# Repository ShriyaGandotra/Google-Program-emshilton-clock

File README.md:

# emshilton-clock
As a part of Google Hardware Sprint Program :
 - Developed Schematic of my clock.
 - Designed PCB using KiCAD software.
 - Followed by testing and documentation of the product.

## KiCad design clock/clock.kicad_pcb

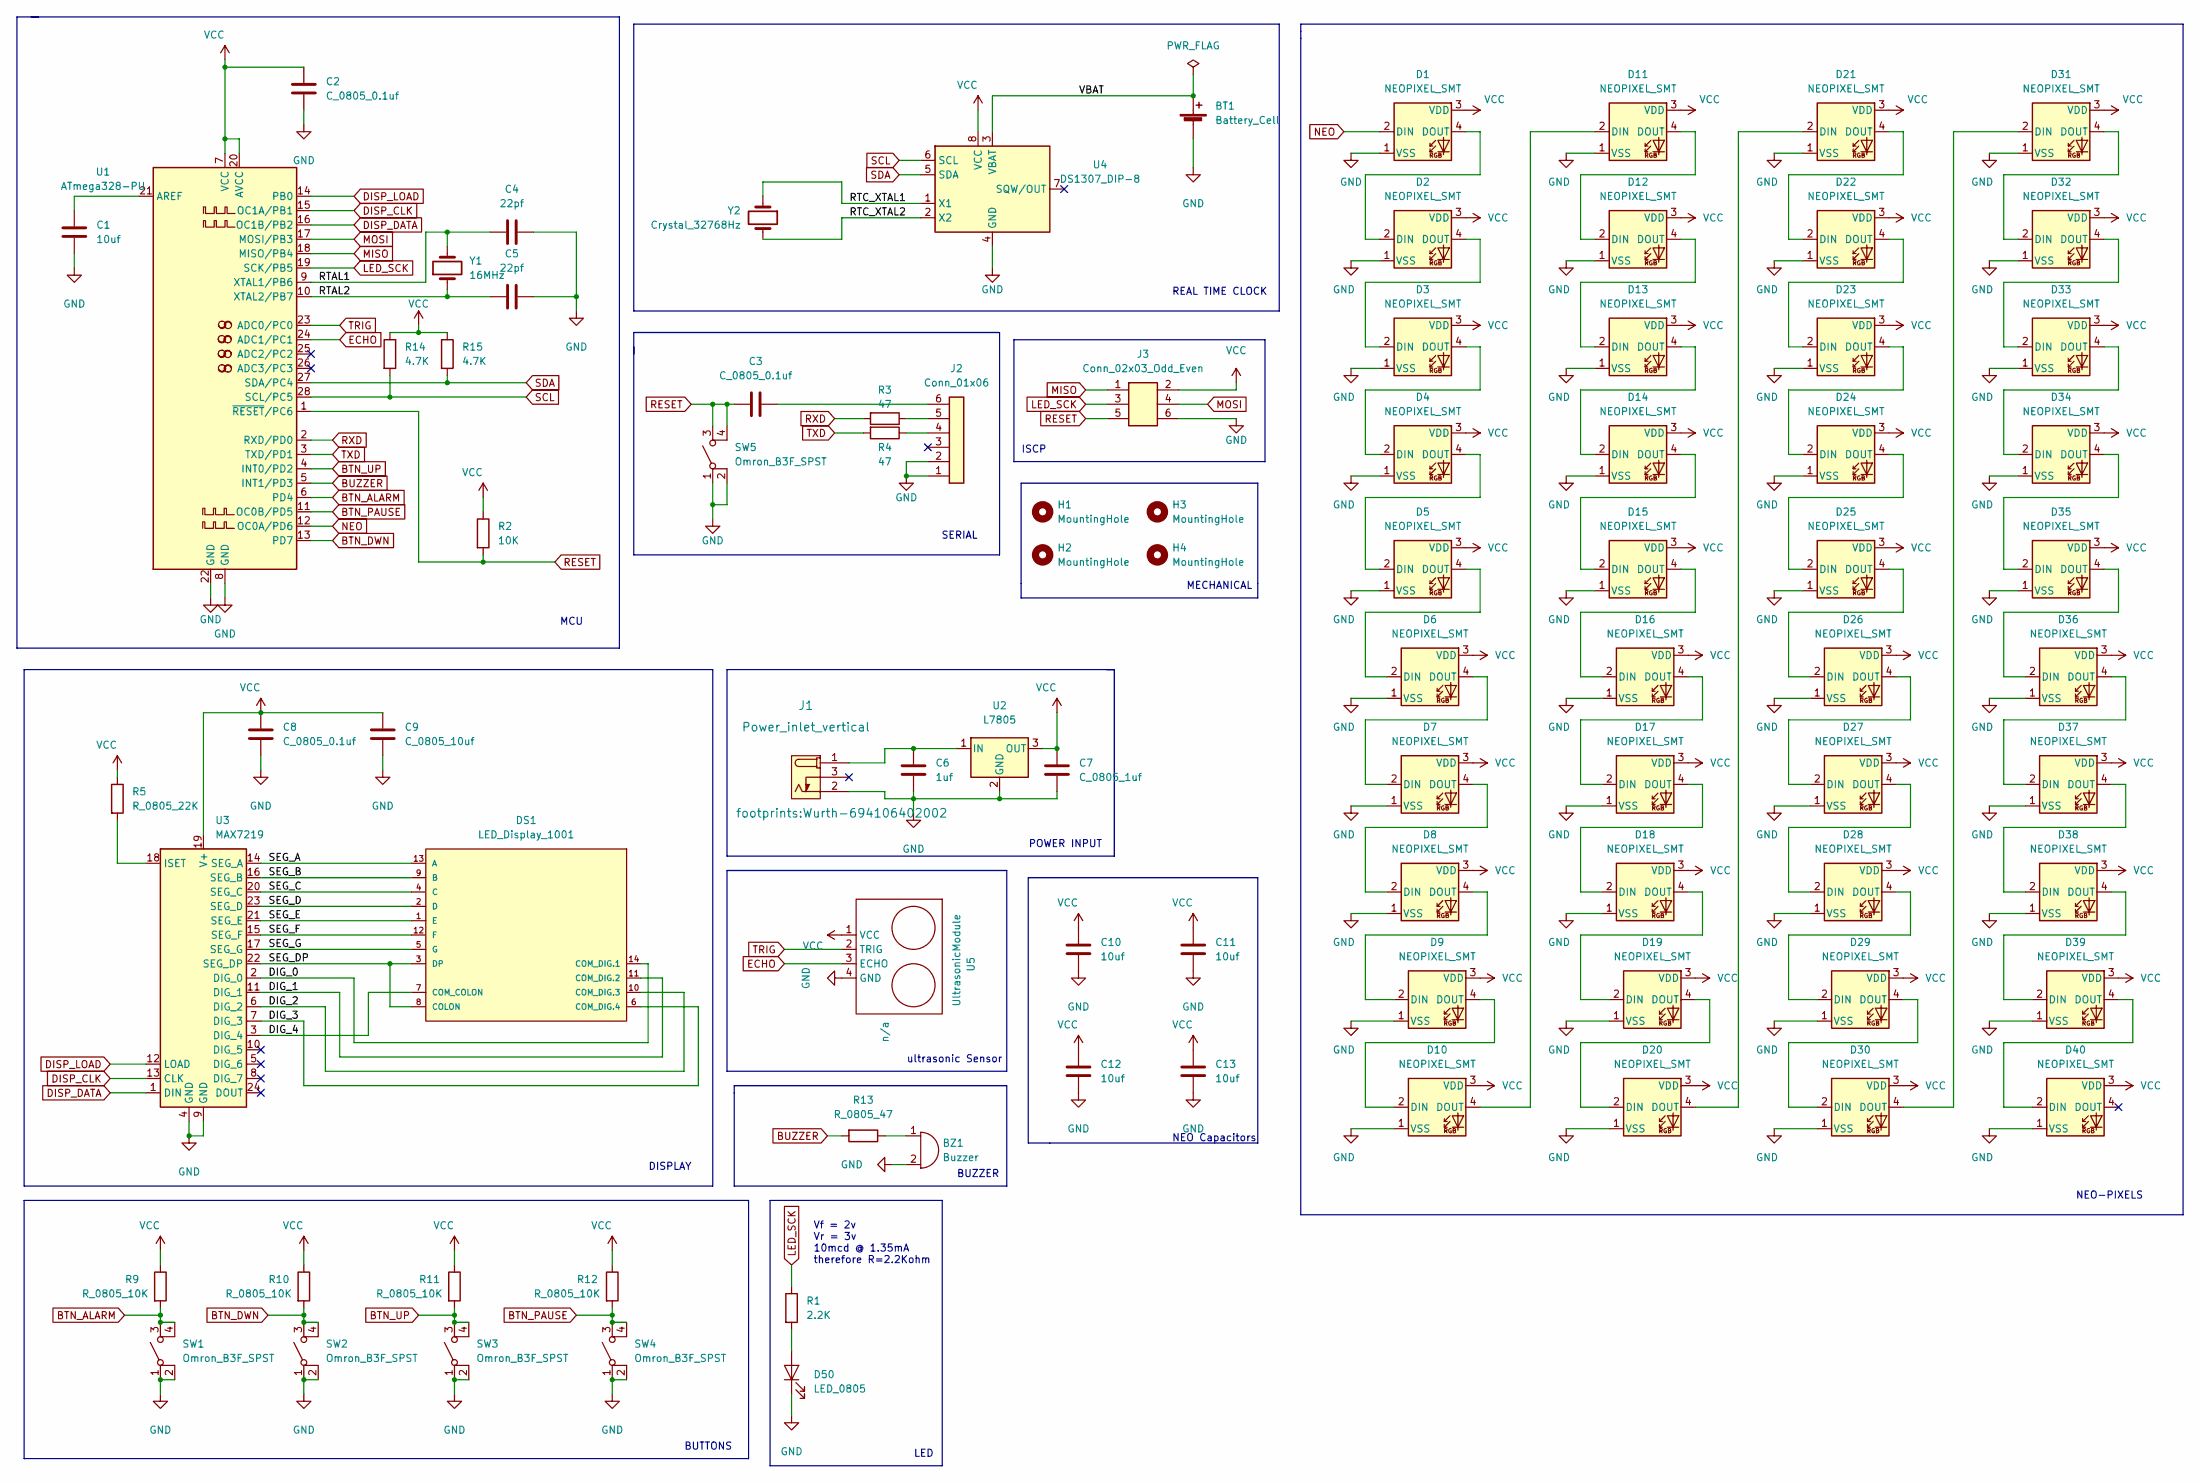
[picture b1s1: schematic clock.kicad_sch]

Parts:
BT1: Battery_Cell; BatteryHolder_Keystone_106_1x20mm; MPN BS-7; Digikey PN BS-7-ND
BZ1: Buzzer; Buzzer_TDK_PS1240P02BT_D12.2mm_H6.5mm; MPN PS1420P02CT; Digikey PN 445-2526-1-ND
C1, C10, C11, C12, C13: 10uf; C_0805_2012Metric; Voltage N/A; Tolerance N/A; MPN GRM21BR61E106KA73L; Digikey PN 490-5523-1-ND
C2, C3, C8: C_0805_0.1uf; C_0805_2012Metric; Voltage N/A; Tolerance N/A; MPN CC0805KKX7R8BB105; Digikey PN 311-1456-1-ND
C4, C5: 22pf; C_0805_2012Metric; Voltage N/A; Tolerance N/A; MPN CC0805JRNPO9BN220; Digikey PN 311-1103-1-ND
C6: 1uf; C_0805_2012Metric; Voltage N/A; Tolerance N/A; MPN CC0805KKX7R8BB105; Digikey PN 311-1456-1-ND
C7: C_0805_1uf; C_0805_2012Metric; Voltage N/A; Tolerance N/A; MPN CC0805KKX7R8BB105; Digikey PN 311-1456-1-ND
C9: C_0805_10uf; C_0805_2012Metric; Voltage N/A; Tolerance N/A; MPN GRM21BR61E106KA73L; Digikey PN 490-5523-1-ND
D1, D2, D3, D4, D5, D6, D7, D8, D9, D10, D11, D12, D13, D14, D15, D16, D17, D18, D19, D20, D21, D22, D23, D24, D25, D26, D27, D28, D29, D30, D31, D32, D33, D34, D35, D36, D37, D38, D39, D40: NEOPIXEL_SMT; LED_SK6812_PLCC4_5.0x5.0mm_P3.2mm; MPN IN-PI554FCH; Digikey PN 1830-1106-1-ND
D50: LED_0805; LED_0805_2012Metric; MPN 150080RS75000; Digikey PN 732-4984-1-ND
DS1: LED_Display_1001; Adafruit-1001-0-0-MFG; forward voltage 3.2V; reverse voltage 5V; mouser part number 485-1001; digikey description WHITE 7-SEGMENT CLOCK DISPLAY
H1, H2, H3, H4: MountingHole; MountingHole_3.2mm_M3
J1: Power_inlet_vertical; Wurth-694106402002; MPN 694106402002; Digikey PN 732-5931-ND
J2: Conn_01x06; PinHeader_1x06_P2.54mm_Vertical; MPN 61300611121; Digikey PN 732-5319-ND
J3: Conn_02x03_Odd_Even; PinHeader_2x03_P2.54mm_Vertical; MPN PRPC003DAAN-RC; Digikey PN S2011EC-03-ND
R1: 2.2K; R_0805_2012Metric; Tolerance N/A; MPN N/A; Digikey PN 311-2.20KCRCT-ND
R2: 10K; R_0805_2012Metric; Tolerance N/A; MPN RC0805FR-0710KL; Digikey PN 311-10.0KCRCT-ND
R3, R4: 47; R_0805_2012Metric; Tolerance N/A; Mouser PN N/A; Digikey PN RC0805FR-0747RL
R5: R_0805_22K; R_0805_2012Metric; Tolerance N/A; MPN RC0805FR-0722KL; Digikey PN 311-22.0KCRCT-ND
R9, R10, R11, R12: R_0805_10K; R_0805_2012Metric; Tolerance N/A; MPN RC0805FR-0710KL; Digikey PN 311-10.0KCRCT-ND
R13: R_0805_47; R_0805_2012Metric; Tolerance N/A; Mouser PN N/A; Digikey PN RC0805FR-0747RL
R14, R15: 4.7K; R_0805_2012Metric; Tolerance N/A; MPN RC0805FR-074K7L; Digikey PN 311-4.70KCRCT-ND
SW1, SW2, SW3, SW4, SW5: Omron_B3F_SPST; SW_SPST_Omron_B3FS-100xP; MPN B3FS-1000P; Digikey PN SW423CT-ND
U1: ATmega328-PU; DIP-28_W7.62mm; MPN ED281DT; Digikey PN ED3050-5-ND
U2: L7805; TO-252-2; MPN L7805CDT-TR; Digikey PN 497-7255-1-ND
U3: MAX7219; DIP-24_W7.62mm; MPN ED241DT; Digikey PN ED3049-5-ND
U4: DS1307_DIP-8; DIP-8_W7.62mm; MPN A 08-LC-TT; Digikey PN AE9986-ND
U5: UltrasonicModule; HC-SR04_Horiz; Digikey PN n/a
Y1: 16MHz; Crystal_SMD_HC49-SD; MPN ECS-160-20-5PXDN-TR; Digikey PN XC1299CT-ND
Y2: Crystal_32768Hz; Crystal_SMD_2Pin_3.2x1.5mm; MPN Q 0,032768-JTX310-12,5-20-T1-HMR-50K-LF; Digikey PN 1908-1314-1-ND

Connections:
/DIG_0: DS1.14 (COM_DIG.1), U3.2 (DIG_0)
/DIG_1: DS1.11 (COM_DIG.2), U3.11 (DIG_1)
/DIG_4: DS1.7 (COM_COLON), U3.3 (DIG_4)
/RTAL1: C4.2, U1.9 (XTAL1/PB6), Y1.2
/RTAL2: C5.2, U1.10 (XTAL2/PB7), Y1.1
/RTC_XTAL1: U4.1 (X1), Y2.1
/RTC_XTAL2: U4.2 (X2), Y2.2
/SEG_A: DS1.13 (A), U3.14 (SEG_A)
/SEG_B: DS1.9 (B), U3.16 (SEG_B)
/SEG_C: DS1.4 (C), U3.20 (SEG_C)
/SEG_D: DS1.2 (D), U3.23 (SEG_D)
/SEG_DP: DS1.3 (DP), DS1.8 (COLON), U3.22 (SEG_DP)
/SEG_E: DS1.1 (E), U3.21 (SEG_E)
/SEG_F: DS1.12 (F), U3.15 (SEG_F)
/SEG_G: DS1.5 (G), U3.17 (SEG_G)
/VBAT: BT1.1 (+), U4.3 (VBAT)
BTN_ALARM: R9.2, SW1.3 (B), SW1.4 (B), U1.6 (PD4)
BTN_DWN: R10.2, SW2.3 (B), SW2.4 (B), U1.13 (PD7)
BTN_PAUSE: R12.2, SW4.3 (B), SW4.4 (B), U1.11 (OC0B/PD5)
BTN_UP: R11.2, SW3.3 (B), SW3.4 (B), U1.4 (INT0/PD2)
BUZZER: R13.2, U1.5 (INT1/PD3)
DISP_CLK: U1.15 (OC1A/PB1), U3.13 (CLK)
DISP_DATA: U1.16 (OC1B/PB2), U3.1 (DIN)
DISP_LOAD: U1.14 (PB0), U3.12 (LOAD)
ECHO: U1.24 (ADC1/PC1), U5.3 (ECHO)
LED_SCK: J3.3, R1.1, U1.19 (SCK/PB5)
MISO: J3.1, U1.18 (MISO/PB4)
MOSI: J3.4, U1.17 (MOSI/PB3)
NEO: D1.2 (DIN), U1.12 (OC0A/PD6)
unnamed: BZ1.1 (-), R13.1
unnamed: C1.1, U1.21 (AREF)
unnamed: C3.1, J2.6
unnamed: C6.1, J1.1 (POLE), U2.1 (IN)
unnamed: D1.4 (DOUT), D2.2 (DIN)
unnamed: D2.4 (DOUT), D3.2 (DIN)
unnamed: D3.4 (DOUT), D4.2 (DIN)
unnamed: D4.4 (DOUT), D5.2 (DIN)
unnamed: D5.4 (DOUT), D6.2 (DIN)
unnamed: D6.4 (DOUT), D7.2 (DIN)
unnamed: D7.4 (DOUT), D8.2 (DIN)
unnamed: D8.4 (DOUT), D9.2 (DIN)
unnamed: D9.4 (DOUT), D10.2 (DIN)
unnamed: D10.4 (DOUT), D11.2 (DIN)
unnamed: D11.4 (DOUT), D12.2 (DIN)
unnamed: D12.4 (DOUT), D13.2 (DIN)
unnamed: D13.4 (DOUT), D14.2 (DIN)
unnamed: D14.4 (DOUT), D15.2 (DIN)
unnamed: D15.4 (DOUT), D16.2 (DIN)
unnamed: D16.4 (DOUT), D17.2 (DIN)
unnamed: D17.4 (DOUT), D18.2 (DIN)
unnamed: D18.4 (DOUT), D19.2 (DIN)
unnamed: D19.4 (DOUT), D20.2 (DIN)
unnamed: D20.4 (DOUT), D21.2 (DIN)
unnamed: D21.4 (DOUT), D22.2 (DIN)
unnamed: D22.4 (DOUT), D23.2 (DIN)
unnamed: D23.4 (DOUT), D24.2 (DIN)
unnamed: D24.4 (DOUT), D25.2 (DIN)
unnamed: D25.4 (DOUT), D26.2 (DIN)
unnamed: D26.4 (DOUT), D27.2 (DIN)
unnamed: D27.4 (DOUT), D28.2 (DIN)
unnamed: D28.4 (DOUT), D29.2 (DIN)
unnamed: D29.4 (DOUT), D30.2 (DIN)
unnamed: D30.4 (DOUT), D31.2 (DIN)
unnamed: D31.4 (DOUT), D32.2 (DIN)
unnamed: D32.4 (DOUT), D33.2 (DIN)
unnamed: D33.4 (DOUT), D34.2 (DIN)
unnamed: D34.4 (DOUT), D35.2 (DIN)
unnamed: D35.4 (DOUT), D36.2 (DIN)
unnamed: D36.4 (DOUT), D37.2 (DIN)
unnamed: D37.4 (DOUT), D38.2 (DIN)
unnamed: D38.4 (DOUT), D39.2 (DIN)
unnamed: D39.4 (DOUT), D40.2 (DIN)
unnamed: D50.2 (A), R1.2
unnamed: J2.4, R4.1
unnamed: J2.5, R3.1
unnamed: R5.2, U3.18 (ISET)
RESET: C3.2, J3.5, R2.2, SW5.3 (B), SW5.4 (B), U1.1 (~RESET/PC6)
RXD: R3.2, U1.2 (RXD/PD0)
SCL: R14.2, U1.28 (SCL/PC5), U4.6 (SCL)
SDA: R15.2, U1.27 (SDA/PC4), U4.5 (SDA)
TRIG: U1.23 (ADC0/PC0), U5.2 (TRIG)
TXD: R4.2, U1.3 (TXD/PD1)
VCC: C2.1, C7.1, C8.1, C9.1, C10.1, C11.1, C12.1, C13.1, D1.3 (VDD), D2.3 (VDD), D3.3 (VDD), D4.3 (VDD), D5.3 (VDD), D6.3 (VDD), D7.3 (VDD), D8.3 (VDD), D9.3 (VDD), D10.3 (VDD), D11.3 (VDD), D12.3 (VDD), D13.3 (VDD), D14.3 (VDD), D15.3 (VDD), D16.3 (VDD), D17.3 (VDD), D18.3 (VDD), D19.3 (VDD), D20.3 (VDD), D21.3 (VDD), D22.3 (VDD), D23.3 (VDD), D24.3 (VDD), D25.3 (VDD), D26.3 (VDD), D27.3 (VDD), D28.3 (VDD), D29.3 (VDD), D30.3 (VDD), D31.3 (VDD), D32.3 (VDD), D33.3 (VDD), D34.3 (VDD), D35.3 (VDD), D36.3 (VDD), D37.3 (VDD), D38.3 (VDD), D39.3 (VDD), D40.3 (VDD), J3.2, R2.1, R5.1, R9.1, R10.1, R11.1, R12.1, R14.1, R15.1, U1.7 (VCC), U1.20 (AVCC), U2.3 (OUT), U3.19 (V+), U4.8 (VCC), U5.1 (VCC)

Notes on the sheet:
Vf = 2v Vr = 3v 10mcd @ 1.35mA therefore R=2.2Kohm
MECHANICAL
BUTTONS
ultrasonic Sensor
ISCP
NEO Capacitors
NEO-PIXELS
POWER INPUT
MCU
SERIAL
BUZZER
REAL TIME CLOCK
DISPLAY
LED

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
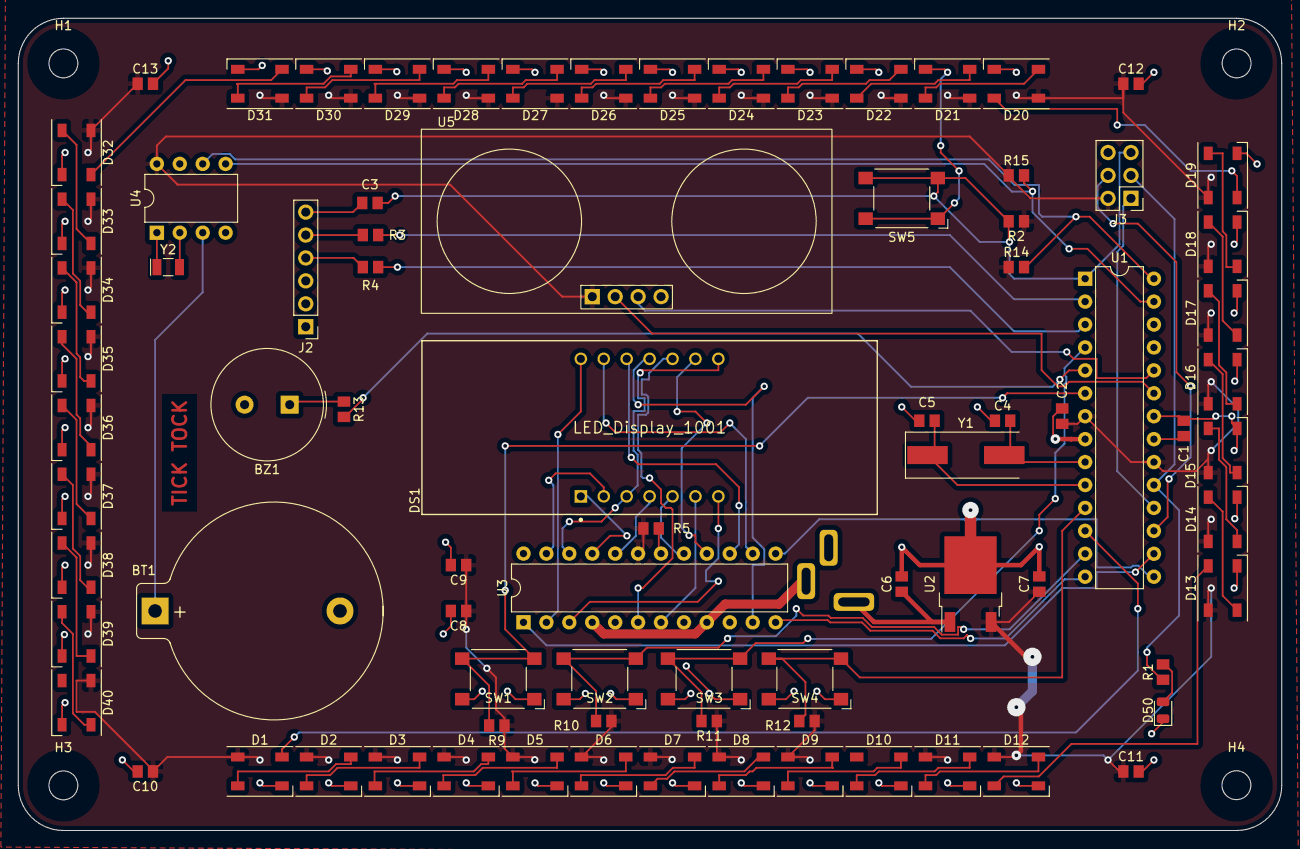
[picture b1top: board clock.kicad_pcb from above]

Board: 2 copper layers, 140.0 x 90.0 mm, 88 parts (1 on the bottom side), 84 nets.

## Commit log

2022-06-07 Clock
2022-06-12 Blinky Led
2022-06-17 CPU, Crystal and power on schematic
2022-06-17 Blinking an Led on Arduino
2022-06-17 Create Blinking Led - Week 1
2022-06-27 Create Button Press- Week 2
2022-06-28 Create RTC module
2022-06-28 Rename RTC module to RTC module - week 3
2022-07-05 update clock
2022-07-14 updated clock
2022-07-19 pcb-changes
2022-07-20 PCB update
2022-07-22 Final Clock Design
